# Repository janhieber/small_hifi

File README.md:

# About
This project is about creating a small HiFi audio system.

We intend to build a two way stereo system (2 boxes, each 2 speakers)
with small size (front not bigger then DIN A4 paper).

The systems purpose is providing good audio quality in small rooms.  
The speakers can be places on a desk besides the computer screen for example.

# System design and architecture
Master box:
- DSP audio crossover with various input cards
- 2 x class D amps, for each speaker one
- Tweeter + mid-range driver

Slave Box:  
Same as master box, but no crossover and input stuff.  
Master box provides the ready to use audio signal and
a data link for slave via SPDIF.

Master box should run in mono mode when
slave is not present.

Edit ``system_architecture.xml`` on [draw.io](https://www.draw.io/)

# Technical
- [Controlboard](controlboard/)
  - Input electronics (USB, BT, analog, ...)
  - STM32 controller (for DSP and other stuff)
  - DAC and volume control
  - Small high quality power supply
- [Amplifier](amplifier/)
  - Class D amplifier
  - High power (switching?) supply
- [Box](box/)
  - Mid-range driver
  - Tweeter
  - Chassis

# Tools
We try to use free tools when possible.

- ECAD/EDA: [KiCAD](http://kicad.org/)
- CAD: [FreeCAD](https://www.freecadweb.org/) or OpenSCAD
- Drawings/charts: [draw.io](https://www.draw.io/)

# Contributing
Most small things may be done in master branche.  
For change/redesign use a dedicated branch!

Example, if you develop a new input board, you can do this on master.
But if you decide to redesign a board or part of a board, make a branch
for it and merge it to master when its finished and proven.

If you are tired of merging in master you can always make a branch for yourself
and merge your work into master when finshed.

We have some good knowledge on making this real, but of course we don't know everything
and we don't want to spend years making this perfect. So if you want to contribute, feel
free to contact us.

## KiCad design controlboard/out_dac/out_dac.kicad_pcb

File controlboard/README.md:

<!-- vim-markdown-toc GFM -->
* [About](#about)
* [Checklist](#checklist)
  * [PCB routing](#pcb-routing)
* [Technical](#technical)
  * [power supply](#power-supply)
  * [Input boards](#input-boards)
  * [STM32F7](#stm32f7)
  * [Out stage](#out-stage)
  * [Nice to have](#nice-to-have)
  * [I2C bus addresses](#i2c-bus-addresses)
* [Tools](#tools)
* [Notes](#notes)

<!-- vim-markdown-toc -->

# About
This is the DSP/control board.  

Hardware desig files are here, [firmware](firmware/) is
in subfolder.

The first step is to design a PCB for every IC
so we can test it with a STM32 dev board.  
The second step is to make a single PCB
when we know things work.

The audio input will be placed un extra PCBs.
We make some I2S + power connectors on the main PCB
and the sources like BT or analog can be conntected
to the main board. PCBs are the same for master and slave
except we don't connect the external audio source PCBs on slave.

# Checklist

### PCB routing

- [ ] STM32F7/H7
- [ ] input board: BT audio
- [ ] input board: analog audio
- [ ] DAC + volume control

# Technical

### power supply
Relais for high power supply: [G6DN-1A DC5](http://www.mouser.com/ds/2/307/en-g6dn-838135.pdf)

We will need 3-5 V. So either we use a 5 V supply
or maybe better a 7-9 V supply with linear regulators
for the ICs.

We may use a toroidal core transformer here for
best supply quality.

Additionaly we may use a small switching supply to
make a power on circuit. Always running the transformator
would be power waste in stand-by mode.

Transformator 6V/12V [FP12-950](http://www.mouser.com/ds/2/410/media-1068242.pdf)

Edit ``PowerSupply.xml`` on [draw.io](https://www.draw.io/)

### Input boards
The input boards will have a unique connector, so
we can plug in the cards we need.  
Signals on the connector: GND, I2S, I2C, SPI, GPIO, UART, supply from trafo.

| Signal | Explanation                  |
|--------|------------------------------|
| I2S    | audio to STM32               |
| I2C    | for communication            |
| SPI    | for communication            |
| UART   | for communication            |
| 1 GPIO | to switch power of the board |

For GPIOs a board can use I2C port expander
[PCF8574](http://www.ti.com/lit/ds/symlink/pcf8574.pdf)

- Analog stereo input with 3.5 mm jack + good ADC
- Bluetooth audio: [Bluegiga WT32i](https://www.silabs.com/products/wireless/bluetooth/bluetooth-classic-modules/wt32i-bluetooth-audio-module)
- USB audio: [CP2615](https://www.silabs.com/documents/public/data-sheets/cp2615-datasheet.pdf)
- Small Linux board with WLAN could provide a Spotify client

### STM32F7
- Should handle the digital inputs (I2S switch)
- Acts as audio crossover for high and middle/low tone (BiQuad IIRs)
- Could do some equalizing etc...
- For analog volume control IC
- Some runtime config of DSP
- Remote control IR/radio: [IRMP](https://github.com/svn2github/irmp)
- Switch on delay to charge caps
- Temperature control

### Out stage
Design files in [out_dac](out_dac)
- DAC: [TI PCM5242](http://www.ti.com/lit/ds/symlink/pcm5242.pdf)
- Volume control: 
TBD: [X9C103](https://www.intersil.com/en/products/data-converters/digital-potentiometers--dcps-/dcps/X9C103.html#documents) 
see: https://www.diy-hifi-forum.eu/forum/showthread.php?14609-Analoge-Lautst%E4rkeregelung-f%FCr-nach-m-DSP-oder-Universal-Vorverst%E4r

Amp has differential inputs.  
We switched to a DAC with differential outputs.  
Now we need a volume control with differential in- and outputs.

### Nice to have
This stuff is low prio!

Display: [Winstar OLED 64x32](http://www.winstar.com.tw/products/oled-module/graphic-oled-display/micro.html)  
Gesture sensor: [APDS-9960](https://cdn.sparkfun.com/datasheets/Sensors/Proximity/apds9960.pdf)

### I2C bus addresses

[I2C](http://www.ti.com/lit/ds/symlink/pcf8574.pdf) port expander has ``0100 xxx`` (0x21 - 0x27).

| Address | Device           |
|----------|-----------------|
| 0x21 | Analog stereo input |
| 0x22 | Bluetooth audio     |
| 0x23 | USB audio           |
| -    | Linux board         |

# Tools
The board should be designed with KiCAD.

KiCAD howtos: [http://kicad.txplore.com/?cat=1](http://kicad.txplore.com/?cat=1)
- [Create parts](http://kicad.txplore.com/?p=96): This is the schematic part, has nothing to do with the footprint.
- [Create footprints](http://kicad.txplore.com/?p=111): Footprint and part is matches by pin numbers.

Parts with much pins can be generated by KiPart from CSV!

# Notes
[https://www.hobbyhifiladen.de/aktivmodule-dsp/sure-electronics/?p=4](https://www.hobbyhifiladen.de/aktivmodule-dsp/sure-electronics/?p=4)

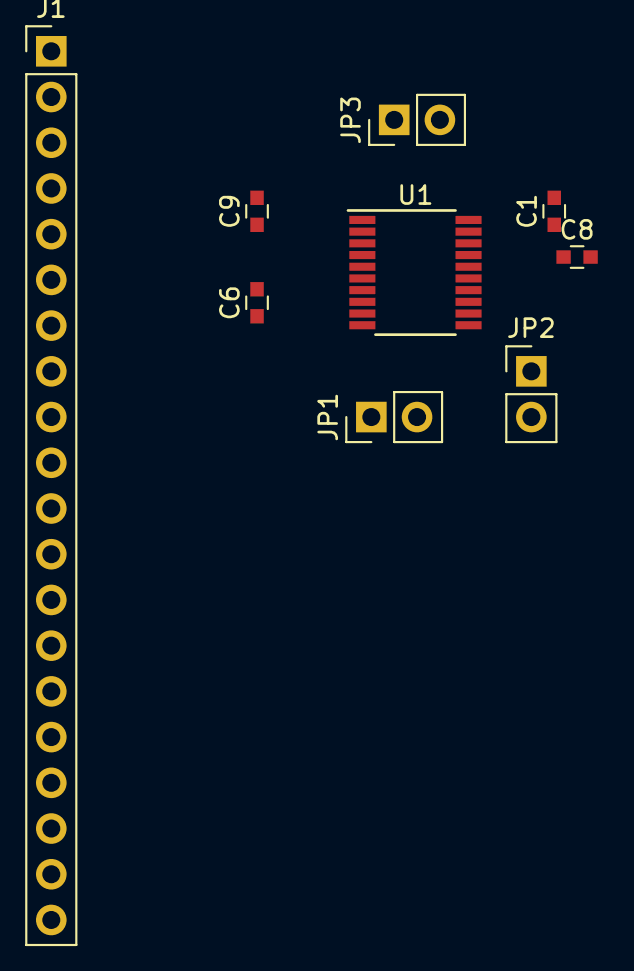
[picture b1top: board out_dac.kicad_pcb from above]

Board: 2 copper layers, 9 parts (0 on the bottom side), 10 nets, no tracks yet.

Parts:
C1, C6, C8, C9: 100n; C_0603
J1: CONN_01X20; Pin_Header_Straight_1x20_Pitch2.54mm
JP1, JP2, JP3: jumper; Pin_Header_Straight_1x02_Pitch2.54mm
U1: PCM5102; TSSOP-20_4.4x6.5mm_Pitch0.65mm

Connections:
+3.3VDAC: C6.2, J1.18, JP3.1, U1.8
+3V3: C1.2, C9.2, J1.20, JP3.2, U1.1, U1.20
/DEMP: J1.2, U1.10
/FLT: J1.4, U1.11
/FMT: J1.3, U1.16
/SCK: JP2.1, U1.12
/XSMT: J1.1, U1.17
GND: C1.1, C8.2, C9.1, J1.19, JP1.2, JP2.2, U1.3, U1.19
GNDA: C6.1, J1.17, JP1.1, U1.9
unnamed: C8.1, U1.18

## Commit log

2017-08-20 add readme
2017-08-20 project structure
2017-08-20 add some info
2017-08-20 add system architecture
2017-08-20 readme update
2017-08-20 add info for micocontroller
2017-08-21 use stm32 as DSP
2017-08-21 update system architecture
2017-08-21 update dsp stuff
2017-08-21 make firmware folder
2017-08-21 some DSP stuff
2017-08-21 systema rch
2017-08-21 update info
2017-08-21 sys arch update
2017-08-21 restructure project
2017-08-21 add dac board KiCAD project
2017-08-22 add USB audio and trafo
2017-08-22 USB audio
2017-08-22 git organisation
2017-08-22 add vol control IC
2017-08-23 info about lib
2017-08-25 add I2C port expander
2017-08-25 add info
2017-08-27 Add Gitter badge
2017-08-27 add amp schematic and tpa symbol
2017-08-27 rename lib
2017-08-28 Add power supply
2017-08-29 Add relais
2017-08-29 Added PowerSupply.xml
2021-11-10 Update README.md
    https://forum.kicad.info/t/warning-avoid-all-links-to-kicad-pcb-org-use-kicad-org/31521
